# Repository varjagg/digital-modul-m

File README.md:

Digital Modul M
===============

An Arduino Pro Mini based controller for Canon EOS 350D covnerted into digital back.

Handles shutter release and ISO selection sequence via a 5 position rotary switch.

Handles shutter release from Leica via M Sync (flashbulb) terminal and triggers shutter release on the Canon.

Emulates phantom limbs of the Canon (feedback from shutter and mirror position sensors).

Still work in progress!

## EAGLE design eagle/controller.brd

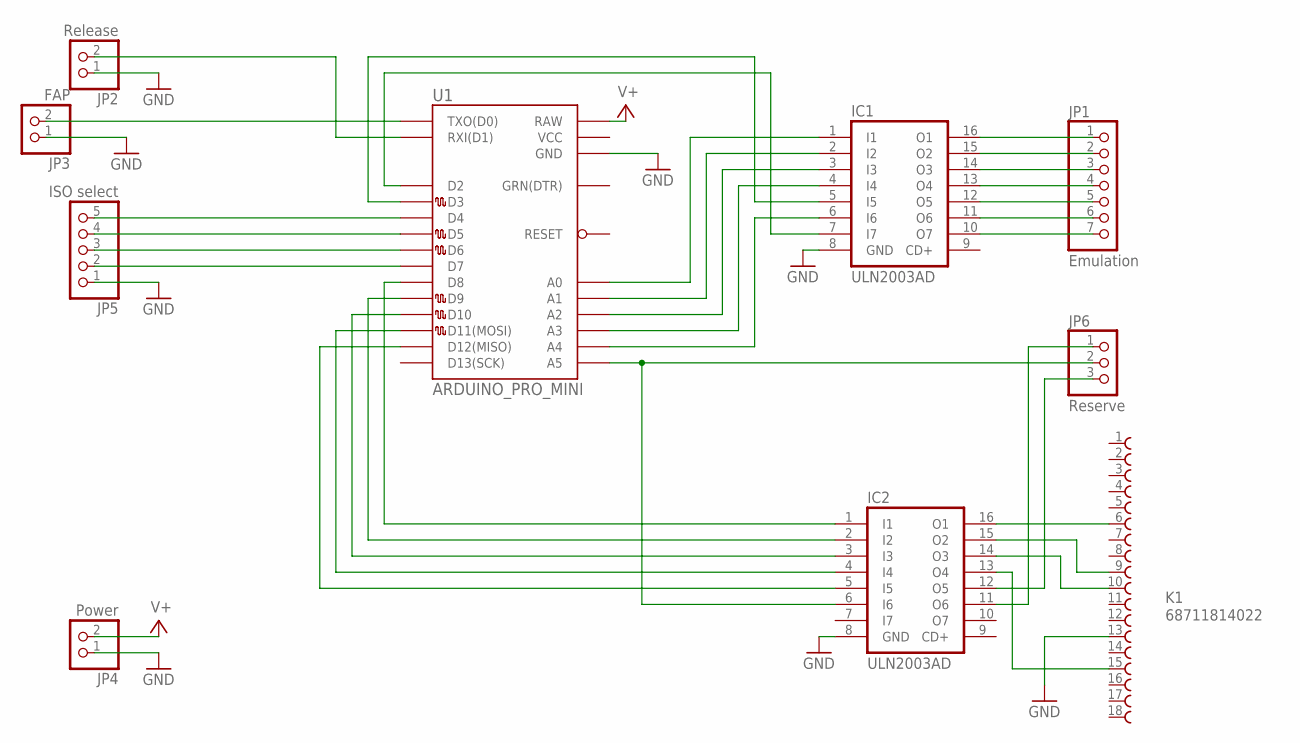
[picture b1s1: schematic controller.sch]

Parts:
IC1, IC2: ULN2003AD; SO16
JP1: Emulation; 1X07/90
JP2: Release; 1X02
JP3: FAP; 1X02
JP4: Power; 1X02
JP5: ISO select; 1X05/90
JP6: Reserve; 1X03
K1: 68711814022
U1: ARDUINO_PRO_MINI

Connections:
GND: IC1.8 (GND), IC2.8 (GND), JP2.1, JP3.1, JP4.1, JP5.1, K1.13, U1.GND1 (GND)
unnamed: IC1.1 (I1), U1.A0
unnamed: IC1.2 (I2), U1.A1
unnamed: IC1.3 (I3), U1.A2
unnamed: IC1.4 (I4), U1.A3
unnamed: IC1.5 (I5), U1.D3
unnamed: IC1.6 (I6), U1.A4
unnamed: IC1.7 (I7), U1.D2
unnamed: IC2.1 (I1), U1.D8
unnamed: IC2.2 (I2), U1.D9
unnamed: IC2.3 (I3), U1.D10
unnamed: IC2.4 (I4), U1.D11 (D11(MOSI))
unnamed: IC2.5 (I5), U1.D12 (D12(MISO))
unnamed: JP5.5, U1.D4
unnamed: JP5.4, U1.D5
unnamed: JP5.3, U1.D6
unnamed: JP5.2, U1.D7
unnamed: JP3.2, U1.TXO (TXO(D0))
unnamed: JP2.2, U1.RXI (RXI(D1))
unnamed: IC2.6 (I6), JP6.2, U1.A5
unnamed: IC1.16 (O1), JP1.1
unnamed: IC1.15 (O2), JP1.2
unnamed: IC1.14 (O3), JP1.3
unnamed: IC1.13 (O4), JP1.4
unnamed: IC1.12 (O5), JP1.5
unnamed: IC1.11 (O6), JP1.6
unnamed: IC1.10 (O7), JP1.7
unnamed: IC2.11 (O6), JP6.1
unnamed: IC2.16 (O1), K1.6
unnamed: IC2.15 (O2), K1.9
unnamed: IC2.14 (O3), K1.10
unnamed: IC2.13 (O4), K1.15
unnamed: IC2.12 (O5), JP6.3
V+: JP4.2, U1.RAW

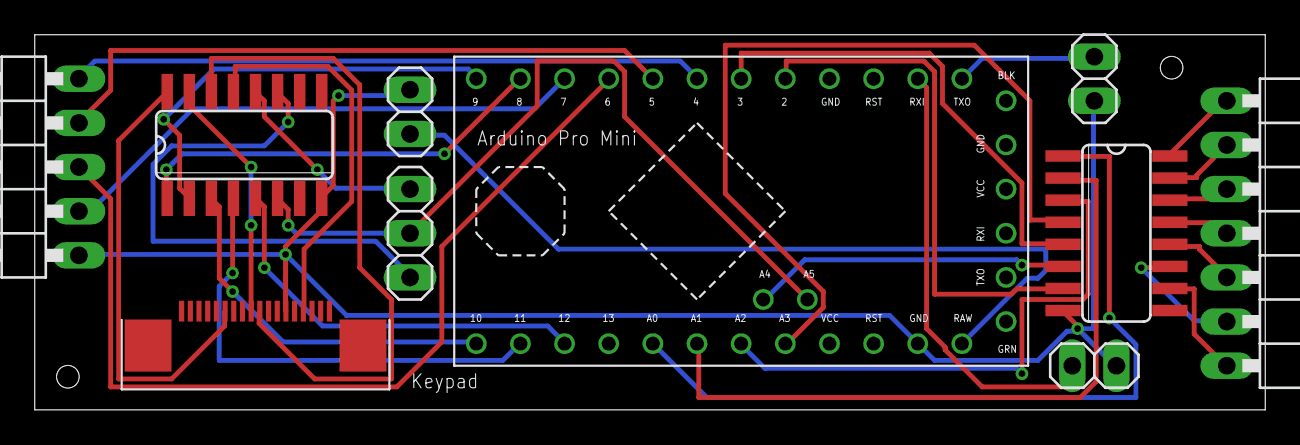
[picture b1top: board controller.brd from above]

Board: 2 copper layers, 70.8 x 21.6 mm, 10 parts (0 on the bottom side), 34 nets.

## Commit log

2013-04-24 initial import
2013-04-24 basic definitions
2013-04-24 expanding the iso sequence
2013-04-24 added shutter sequence and main loop code
2013-04-24 added GPL terms
2013-04-24 shutter release setup
2013-04-24 changed iso set implementation
2013-04-26 fixing the iso selection
2013-04-26 iso button is the up button
2013-05-02 added debug tracing
2013-05-08 bug fixes
2013-05-08 LED trace
2013-05-09 added phantom limbs
2013-05-10 added prerelease, removed debounce of shutter
2013-05-15 changed shutter and mirror control
2013-05-22 moved implementation to smaller arduino mini pro 3.3v
2013-05-22 fixed the pin assignments
2013-05-22 fixed the pin assignments again
2013-05-22 added pixel peeping
2013-05-24 minor tweaks
2013-05-24 more blinkenlichts
2013-05-24 debug
2013-05-24 Fixes ISO selector bug
2013-05-28 added some captures
2013-05-28 removed file
2013-05-28 added control pcb shot
2013-05-31 added switched output diagram
2013-06-07 introduced startup delay
2013-06-07 debugging on live hw
2013-06-07 Close shutter before mirror is up
2013-06-14 First working version
    Capture without physical shutter and mirror assembly now works, but stalls with Error99 on 4th shot.
2013-06-14 Adding back BTN_PRERELEASE
2013-07-02 pcb schematics import
2013-07-02 added BOM
2013-07-03 adjustments, new macros
2013-07-11 a working version with pre-release control - still fails at 4th shot
2013-07-11 a version with direct connection without switches
2013-07-12 direct connection version, fixes ERROR99 issue and performs complete shutter and mirror emulation
2013-07-12 reduced trigger delay to 15ms
2013-07-15 schematics added
2013-07-15 routed the board, updated bom
2013-07-16 changed pin assignments
2013-07-17 removed a glitch in initialization sequence
2013-07-17 changes to iso switch decoding
2013-07-19 updated schematics
2013-07-22 traced the board
2013-08-06 production board REVA
2013-08-30 inverting signals for ULN2003
2013-09-20 new iso switching code
2013-09-30 changes with iso decoding
2014-01-03 disabled serial
2014-05-05 Update dmm.ino
    Added Canon PCBs power control.
2014-07-12 Trimmed the lag timings to shortest possible
    Also fixed the ERROR99 when starting up with sync cable plugged in.
2014-09-18 added build images
2015-03-12 cleaned up dead code
2015-03-12 added shutter shpeed sync mod

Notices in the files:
parts and their libraries:
Wuerth_Elektronik_eiCan_03_ZIF_Connector: Copyright: Würth Elektronik
